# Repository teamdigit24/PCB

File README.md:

# PCB

The OneSense Arduino program is a simple program that tests each sensor connector individually

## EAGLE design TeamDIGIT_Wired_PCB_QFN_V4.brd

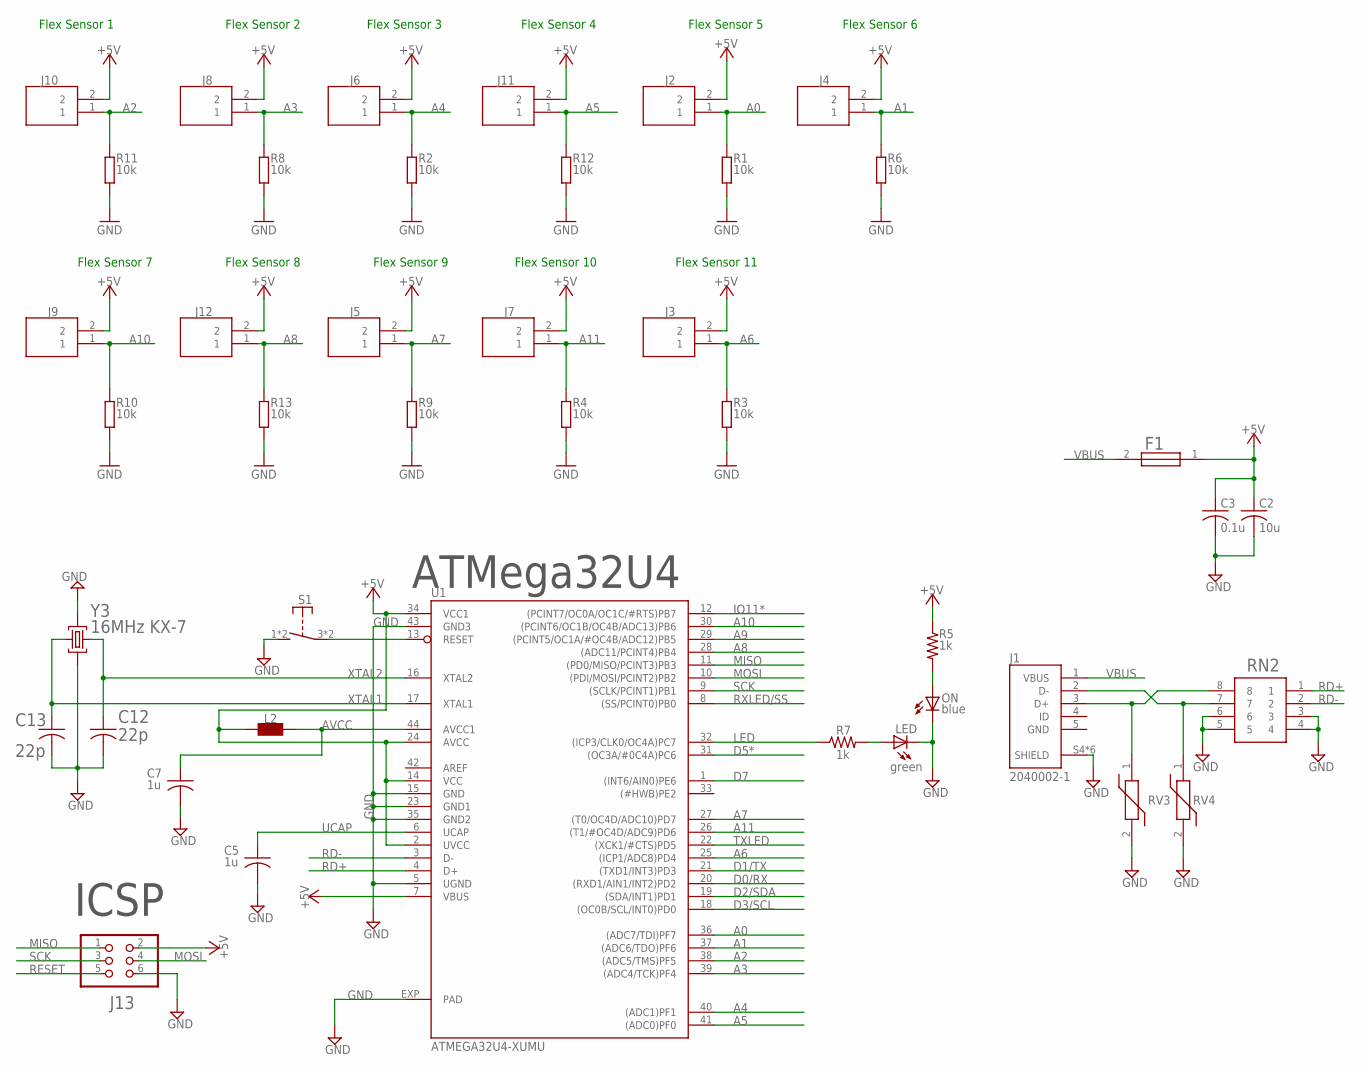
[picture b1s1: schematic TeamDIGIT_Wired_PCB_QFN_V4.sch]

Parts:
C2: 10u; C0603
C3: 0.1u; C0603
C5, C7: 1u; C0603
C12, C13: 22p; C0603
F1: MF-MSMF050-2; FUSC4632X85N
J1: 2040002-1; TE_2040002-1
J2, J3, J4, J5, J6, J7, J8, J9, J10, J11, J12: 6-440054-2; RHDR2W97P0X254_1X2_654X508X137
J13: 3x2M; 2X03
L2: MH2029-300Y; 0805
LED: green; CHIPLED_0805
ON: blue; CHIPLED_0805
R1, R2, R3, R4, R6, R8, R9, R10, R11, R12, R13: 10k; R0603
R5, R7: 1k; R0603
RN2: CAY16-220J4LF; CAY1647R0F4LF
RV3, RV4: CG0603MLC-05E; VARC1608X55N
S1: 434123025826
U1: ATMEGA32U4-XUMU; QFN44ML7X7
Y3: 16MHz KX-7; CRYSTAL-3.2-2.5

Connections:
+5V: C2.1, C3.1, F1.1, J2.2, J3.2, J4.2, J5.2, J6.2, J7.2, J8.2, J9.2, J10.2, J11.2, J12.2, J13.2, L2.1, R5.1, U1.2 (UVCC), U1.7 (VBUS), U1.14 (VCC), U1.24 (AVCC), U1.34 (VCC1)
A0: J2.1, R1.2, U1.36 ((ADC7/TDI)PF7)
A1: J4.1, R6.2, U1.37 ((ADC6/TDO)PF6)
A2: J10.1, R11.2, U1.38 ((ADC5/TMS)PF5)
A3: J8.1, R8.2, U1.39 ((ADC4/TCK)PF4)
A4: J6.1, R2.2, U1.40 ((ADC1)PF1)
A5: J11.1, R12.2, U1.41 ((ADC0)PF0)
A6: J3.1, R3.2, U1.25 ((ICP1/ADC8)PD4)
A7: J5.1, R9.2, U1.27 ((T0/OC4D/ADC10)PD7)
A8: J12.1, R13.2, U1.28 ((ADC11/PCINT4)PB4)
A9: U1.29 ((PCINT5/OC1A/#OC4B/ADC12)PB5)
A10: J9.1, R10.2, U1.30 ((PCINT6/OC1B/OC4B/ADC13)PB6)
A11: J7.1, R4.2, U1.26 ((T1/#OC4D/ADC9)PD6)
AREF: U1.42 (AREF)
AVCC: C7.1, L2.2, U1.44 (AVCC1)
D0/RX: U1.20 ((RXD1/AIN1/INT2)PD2)
D1/TX: U1.21 ((TXD1/INT3)PD3)
D2/SDA: U1.19 ((SDA/INT1)PD1)
D3/SCL: U1.18 ((OC0B/SCL/INT0)PD0)
D5*: U1.31 ((OC3A/#0C4A)PC6)
D7: U1.1 ((INT6/AIN0)PE6)
D+: J1.3 (D+), RN2.8, RV3.1
D-: J1.2 (D-), RN2.7, RV4.1
GND: C2.2, C3.2, C5.2, C7.2, C12.2, C13.2, J1.5 (GND), J1.S4 (SHIELD), J1.S5 (SHIELD), J1.SH1 (SHIELD), J1.SH2 (SHIELD), J1.SH3 (SHIELD), J1.SH4 (SHIELD), J13.6, LED.C, ON.C, R1.1, R2.1, R3.1, R4.1, R6.1, R8.1, R9.1, R10.1, R11.1, R12.1, R13.1, RN2.3, RN2.4, RN2.5, RN2.6, RV3.2, RV4.2, S1.1 (S), S1.2 (S), U1.5 (UGND), U1.15 (GND), U1.23 (GND1), U1.35 (GND2), U1.43 (GND3), U1.EXP (PAD), Y3.2 (GND), Y3.4 (GND)
IO11*: U1.12 ((PCINT7/OC0A/OC1C/#RTS)PB7)
LED: R7.1, U1.32 ((ICP3/CLK0/OC4A)PC7)
MISO: J13.1, U1.11 ((PD0/MISO/PCINT3)PB3)
MOSI: J13.4, U1.10 ((PDI/MOSI/PCINT2)PB2)
unnamed: ON.A, R5.2
unnamed: LED.A, R7.2
RD+: RN2.1, U1.4 (D+)
RD-: RN2.2, U1.3 (D-)
RESET: J13.5, S1.3, S1.4, U1.13 (RESET)
RXLED/SS: U1.8 ((SS/PCINT0)PB0)
SCK: J13.3, U1.9 ((SCLK/PCINT1)PB1)
TXLED: U1.22 ((XCK1/#CTS)PD5)
UCAP: C5.1, U1.6 (UCAP)
VBUS: F1.2, J1.1 (VBUS)
XTAL1: C13.1, U1.17 (XTAL1), Y3.1 (C1)
XTAL2: C12.1, U1.16 (XTAL2), Y3.3 (C2)

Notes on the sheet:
ATMega32U4
ICSP
Flex Sensor 1
Flex Sensor 2
Flex Sensor 3
Flex Sensor 4
Flex Sensor 5
Flex Sensor 6
Flex Sensor 7
Flex Sensor 8
Flex Sensor 9
Flex Sensor 10
Flex Sensor 11

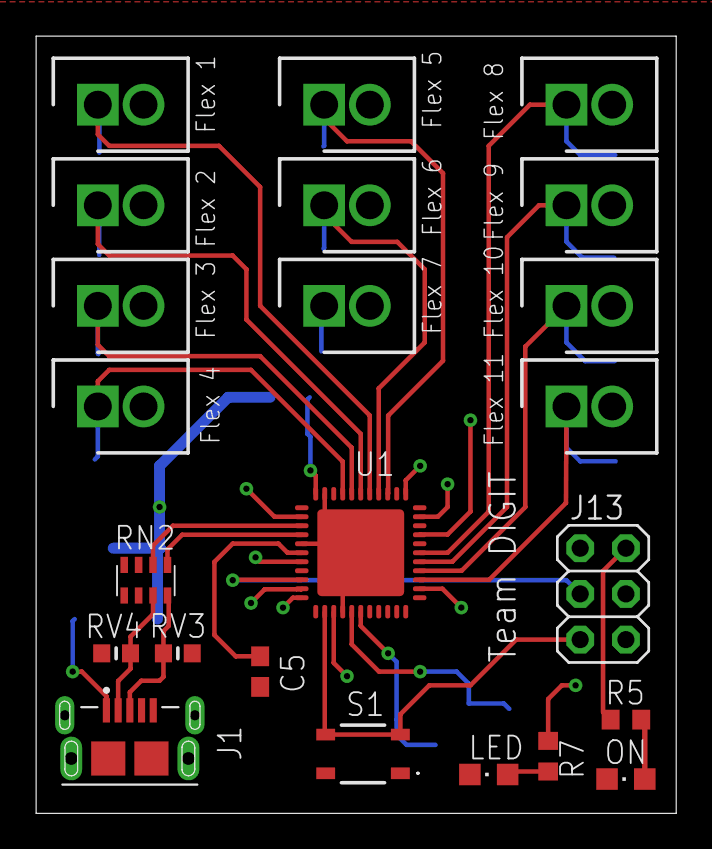
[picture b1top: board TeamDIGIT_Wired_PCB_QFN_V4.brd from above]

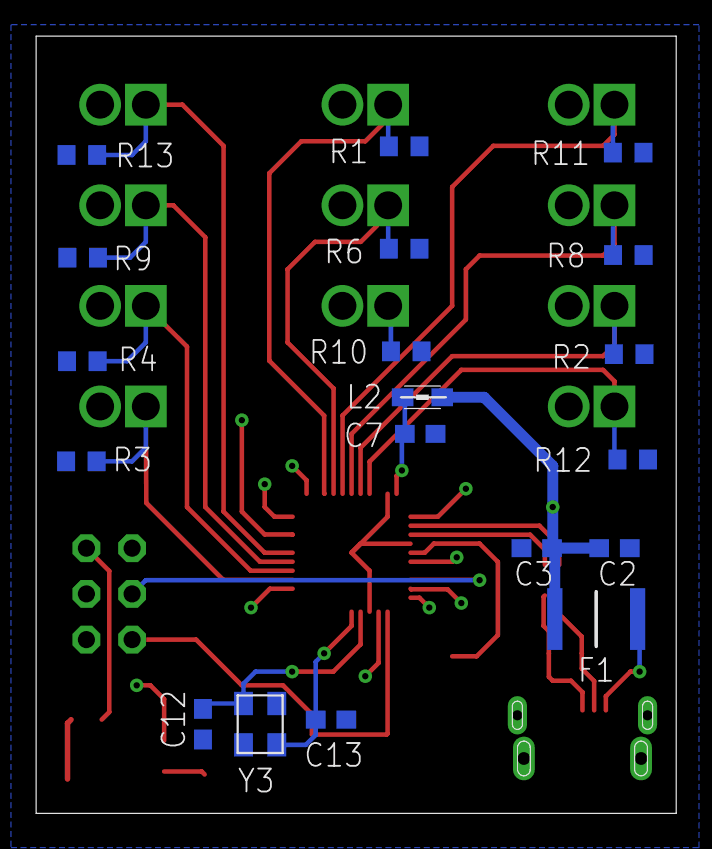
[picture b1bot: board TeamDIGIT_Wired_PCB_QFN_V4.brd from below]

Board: 4 copper layers, 35.6 x 43.2 mm, 42 parts (19 on the bottom side), 29 nets.

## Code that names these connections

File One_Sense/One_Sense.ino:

/*
 * This program was written to test the sensor connections of the PCB. An ADC reading of zero indicates the sensor is not 
 * connected, and an ADC reading of about 450-650 indicates a sensor is connected and reading at a flat angle. A resistance measurement of 
 * infinite indicates that the sensor is disconnected. A resistance measurement of anything for 8k ohms indicates the sensors are connected.
 */

const int FLEX_1 = A2;
const int FLEX_2 = A3;
const int FLEX_3 = A4;
const int FLEX_4 = A5;
const int FLEX_5 = A0;
const int FLEX_6 = A1;
const int FLEX_7 = A10;
const int FLEX_8 = A8;
const int FLEX_9 = A7;
const int FLEX_10 = A11;
const int FLEX_11 = A6;

/*
 
A0 = D18 
A1 = D19
A2 = D20
A3 = D21
A4 = D22
A5 = D23
A6 = D4 = PD4
A7 = D6 = PD7
A8 = D8 = PB4 
A9 = D9 = PB5
A10 = D10 = PB6
A11 = D12 = PD6

*/


const int samplingRateMs = 1000;     //sampling rate of 1s.
const float seriesResistor = 10000.0; //10k resistor from voltage dividing circuit
const float VCC = 5.0;
const float STRAIGHT_RESISTANCE = 10000.0; // resistance when straight
const float BEND_RESISTANCE = 14000.0;    // resistance at 90 deg
float COUNTS = 0;

void setup() {
  // put your setup code here, to run once:
  Serial.begin(9600);
  analogReference(DEFAULT);
  pinMode(FLEX_1,INPUT);
  pinMode(FLEX_2,INPUT);
  pinMode(FLEX_3,INPUT);
  pinMode(FLEX_4,INPUT);
  pinMode(FLEX_5,INPUT);
  pinMode(FLEX_6,INPUT);
  pinMode(FLEX_7,INPUT);
  pinMode(FLEX_8,INPUT);
  pinMode(FLEX_9,INPUT);
  pinMode(FLEX_10,INPUT);
  pinMode(FLEX_11,INPUT);
  Serial.println("Hit any key to receive a new reading");
}

void loop() {
  // put your main code here, to run repeatedly:
  static unsigned long samplingTimerMs = millis();
  if(millis() - samplingTimerMs >= samplingRateMs)
  { 
    //Serial.println(analogRead(FLEX_11));
    samplingTimerMs = millis();
    
    Serial.println ("Reading all flex sensors...");     // signal initalization done
    Serial.println(" ");
    Serial.print("Flex Sensor 1:  "); Serial.println((float)(seriesResistor * (VCC / (analogRead(FLEX_1) * VCC /1023.0) - 1.0)));
    Serial.print("Flex Sensor 2:  "); Serial.println((float)(seriesResistor * (VCC / (analogRead(FLEX_2) * VCC /1023.0) - 1.0)));
    Serial.print("Flex Sensor 3:  "); Serial.println((float)(seriesResistor * (VCC / (analogRead(FLEX_3) * VCC /1023.0) - 1.0)));
    Serial.print("Flex Sensor 4:  "); Serial.println((float)(seriesResistor * (VCC / (analogRead(FLEX_4) * VCC /1023.0) - 1.0)));
    Serial.print("Flex Sensor 5:  "); Serial.println((float)(seriesResistor * (VCC / (analogRead(FLEX_5) * VCC /1023.0) - 1.0)));
    Serial.print("Flex Sensor 6:  "); Serial.println((float)(seriesResistor * (VCC / (analogRead(FLEX_6) * VCC /1023.0) - 1.0)));
    Serial.print("Flex Sensor 7:  "); Serial.println((float)(seriesResistor * (VCC / (analogRead(FLEX_7) * VCC /1023.0) - 1.0)));
    Serial.print("Flex Sensor 8:  "); Serial.println((float)(seriesResistor * (VCC / (analogRead(FLEX_8) * VCC /1023.0) - 1.0)));
    Serial.print("Flex Sensor 9:  "); Serial.println((float)(seriesResistor * (VCC / (analogRead(FLEX_9) * VCC /1023.0) - 1.0)));
    Serial.print("Flex Sensor 10: "); Serial.println((float)(seriesResistor * (VCC / (analogRead(FLEX_10) * VCC /1023.0) - 1.0)));
    Serial.print("Flex Sensor 11: "); Serial.println((float)(seriesResistor * (VCC / (analogRead(FLEX_11) * VCC /1023.0) - 1.0)));
    Serial.println("Hit any key to receive a new reading");
    Serial.println(" ");
    while(Serial.available() == 0){}
    char input = Serial.read();
    //Serial.println(input);
    //char dump = Serial.read();
    
  }//timer loop
}//loop

/*
 * This function gives the user the option to read the resistance
 */
float ReadResistance(float SENSOR)
{
  float voltage = analogRead(SENSOR) * VCC /1023.0;
  return (float)(seriesResistor * (VCC / (analogRead(SENSOR) * VCC /1023.0) - 1.0));
}

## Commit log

2022-11-19 added files via upload
